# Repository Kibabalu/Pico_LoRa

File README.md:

# Pico LoRa Node

LoRa Node based on Raspberry Pi Pico and LoRa board RFM95

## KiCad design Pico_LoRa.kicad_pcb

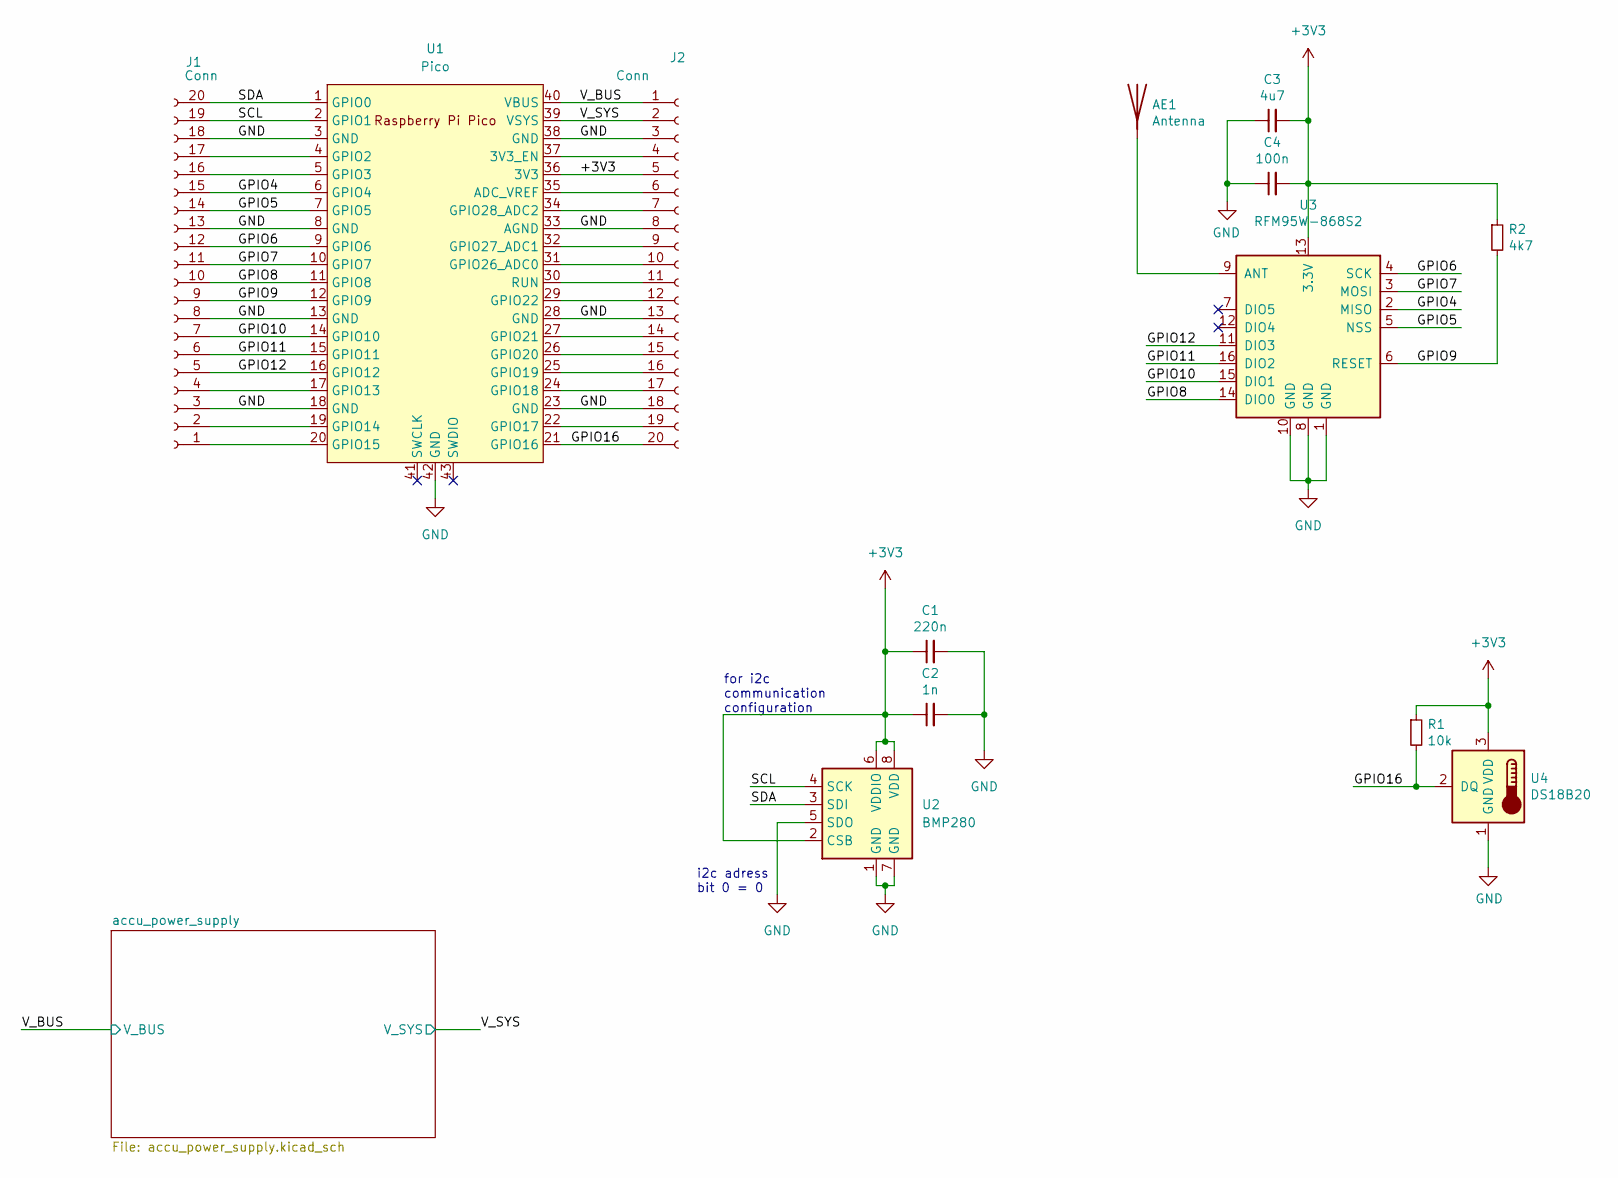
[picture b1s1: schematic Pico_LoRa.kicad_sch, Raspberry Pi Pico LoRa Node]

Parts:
AE1: Antenna; PinHeader_1x01_P2.54mm_Vertical
C1: 220n; C_0805_2012Metric_Pad1.18x1.45mm_HandSolder
C2: 1n; C_0805_2012Metric_Pad1.18x1.45mm_HandSolder
C3: 4u7; C_0805_2012Metric_Pad1.18x1.45mm_HandSolder
C4: 100n; C_0805_2012Metric_Pad1.18x1.45mm_HandSolder
J1, J2: Conn; PinSocket_1x20_P2.54mm_Vertical
R1: 10k; R_0805_2012Metric_Pad1.20x1.40mm_HandSolder
R2: 4k7; R_0805_2012Metric_Pad1.20x1.40mm_HandSolder
U1: Pico; RPi_Pico_SMD_TH
U2: BMP280; Bosch_LGA-8_2x2.5mm_P0.65mm_ClockwisePinNumbering
U3: RFM95W-868S2; HOPERF_RFM9XW_SMD
U4: DS18B20; TO-92_Inline

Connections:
+3V3: C1.1, C2.1, C3.2, C4.2, J2.5, R1.1, R2.1, U1.36 (3V3), U2.2 (CSB), U2.6 (VDDIO), U2.8 (VDD), U3.13 (3.3V), U4.3 (VDD)
/GPIO4: J1.15, U1.6 (GPIO4), U3.2 (MISO)
/GPIO5: J1.14, U1.7 (GPIO5), U3.5 (NSS)
/GPIO6: J1.12, U1.9 (GPIO6), U3.4 (SCK)
/GPIO7: J1.11, U1.10 (GPIO7), U3.3 (MOSI)
/GPIO8: J1.10, U1.11 (GPIO8), U3.14 (DIO0)
/GPIO9: J1.9, R2.2, U1.12 (GPIO9), U3.6 (RESET)
/GPIO10: J1.7, U1.14 (GPIO10), U3.15 (DIO1)
/GPIO11: J1.6, U1.15 (GPIO11), U3.16 (DIO2)
/GPIO12: J1.5, U1.16 (GPIO12), U3.11 (DIO3)
/GPIO16: J2.20, R1.2, U1.21 (GPIO16), U4.2 (DQ)
/SCL: J1.19, U1.2 (GPIO1), U2.4 (SCK)
/SDA: J1.20, U1.1 (GPIO0), U2.3 (SDI)
/V_BUS: J2.1, U1.40 (VBUS); also elsewhere on the board
/V_SYS: J2.2, U1.39 (VSYS); also elsewhere on the board
GND: C1.2, C2.2, C3.1, C4.1, J1.3, J1.8, J1.13, J1.18, J2.3, J2.8, J2.13, J2.18, U1.3 (GND), U1.8 (GND), U1.13 (GND), U1.18 (GND), U1.23 (GND), U1.28 (GND), U1.33 (AGND), U1.38 (GND), U1.42 (GND), U2.1 (GND), U2.5 (SDO), U2.7 (GND), U3.1 (GND), U3.8 (GND), U3.10 (GND), U4.1 (GND); also elsewhere on the board
unnamed: AE1.1 (A), U3.9 (ANT)
unnamed: J1.1, U1.20 (GPIO15)
unnamed: J1.2, U1.19 (GPIO14)
unnamed: J1.4, U1.17 (GPIO13)
unnamed: J1.16, U1.5 (GPIO3)
unnamed: J1.17, U1.4 (GPIO2)
unnamed: J2.4, U1.37 (3V3_EN)
unnamed: J2.6, U1.35 (ADC_VREF)
unnamed: J2.7, U1.34 (GPIO28_ADC2)
unnamed: J2.9, U1.32 (GPIO27_ADC1)
unnamed: J2.10, U1.31 (GPIO26_ADC0)
unnamed: J2.11, U1.30 (RUN)
unnamed: J2.12, U1.29 (GPIO22)
unnamed: J2.14, U1.27 (GPIO21)
unnamed: J2.15, U1.26 (GPIO20)
unnamed: J2.16, U1.25 (GPIO19)
unnamed: J2.17, U1.24 (GPIO18)
unnamed: J2.19, U1.22 (GPIO17)

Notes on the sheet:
for i2c communication configuration
i2c adress bit 0 = 0

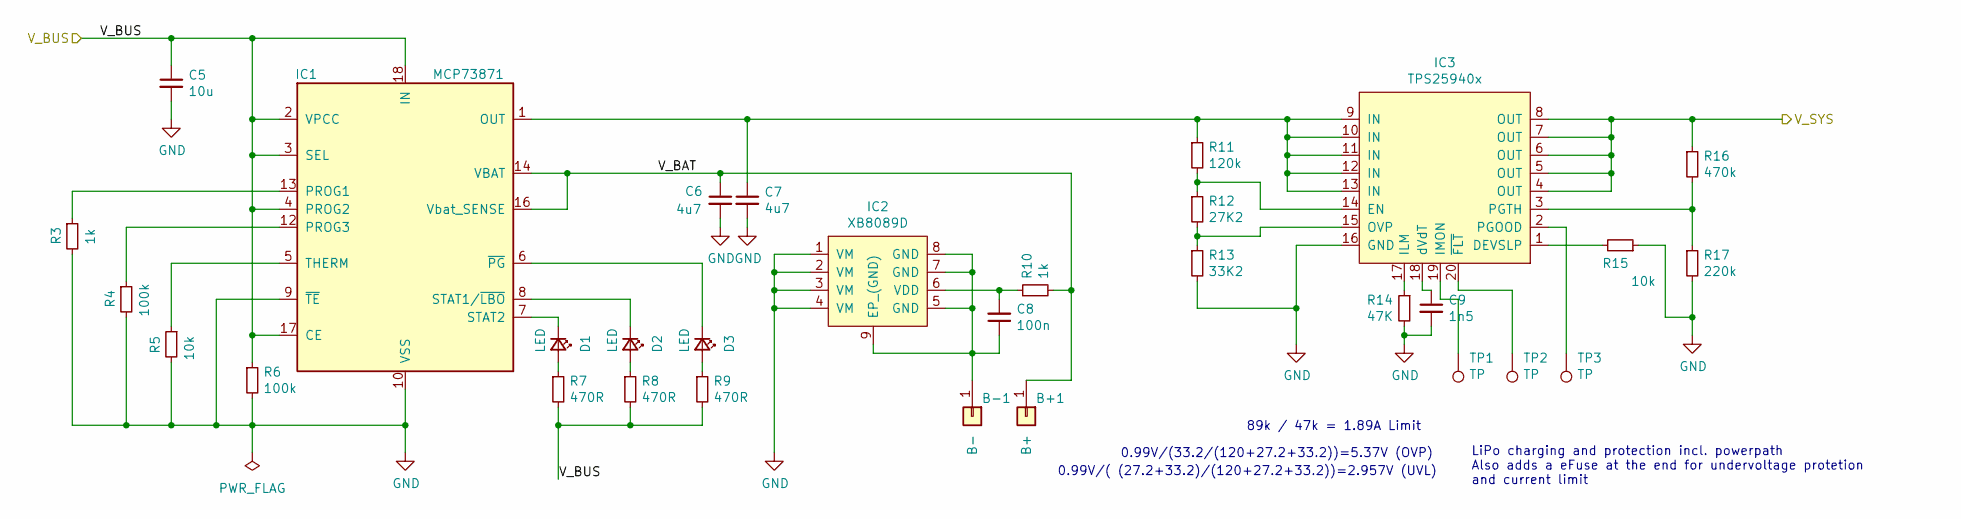
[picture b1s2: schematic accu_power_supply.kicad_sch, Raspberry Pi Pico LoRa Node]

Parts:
B+1: B+; SolderWirePad_1x01_SMD_1x2mm
B-1: B-; SolderWirePad_1x01_SMD_1x2mm
C5: 10u; C_0805_2012Metric_Pad1.18x1.45mm_HandSolder
C6, C7: 4u7; C_0805_2012Metric_Pad1.18x1.45mm_HandSolder
C8: 100n; C_0805_2012Metric_Pad1.18x1.45mm_HandSolder
C9: 1n5; C_0805_2012Metric_Pad1.18x1.45mm_HandSolder
D1, D2, D3: LED; LED_0805_2012Metric_Pad1.15x1.40mm_HandSolder
IC1: MCP73871; QFN-20-1EP_4x4mm_P0.5mm_EP2.5x2.5mm
IC2: XB8089D
IC3: TPS25940x; TI_WQFN_20_EP
R3, R10: 1k; R_0805_2012Metric_Pad1.20x1.40mm_HandSolder
R4, R6: 100k; R_0805_2012Metric_Pad1.20x1.40mm_HandSolder
R5, R15: 10k; R_0805_2012Metric_Pad1.20x1.40mm_HandSolder
R7, R8, R9: 470R; R_0805_2012Metric_Pad1.20x1.40mm_HandSolder
R11: 120k; R_0805_2012Metric_Pad1.20x1.40mm_HandSolder
R12: 27K2; R_0805_2012Metric_Pad1.20x1.40mm_HandSolder
R13: 33K2; R_0805_2012Metric_Pad1.20x1.40mm_HandSolder
R14: 47K; R_0805_2012Metric_Pad1.20x1.40mm_HandSolder
R16: 470k; R_0805_2012Metric_Pad1.20x1.40mm_HandSolder
R17: 220k; R_0805_2012Metric_Pad1.20x1.40mm_HandSolder
TP1, TP2, TP3: TP; TestPoint_Pad_D1.0mm

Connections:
/V_BUS: C5.1, IC1.2 (VPCC), IC1.3 (SEL), IC1.4 (PROG2), IC1.17 (CE), IC1.18 (IN), IC1.19 (IN), R6.1, R7.2, R8.2, R9.2; also elsewhere on the board
/V_SYS: IC3.4 (OUT), IC3.5 (OUT), IC3.6 (OUT), IC3.7 (OUT), IC3.8 (OUT), R16.1; also elsewhere on the board
/accu_power_supply/V_BAT: B+1.1, C6.1, IC1.14 (VBAT), IC1.15 (VBAT), IC1.16 (Vbat_SENSE), R10.2
GND: C5.2, C6.2, C7.2, C9.2, IC1.9 (~TE), IC1.10 (VSS), IC1.11 (VSS), IC1.21 (VSS), IC2.1 (VM), IC2.2 (VM), IC2.3 (VM), IC2.4 (VM), IC3.16 (GND), R3.2, R4.2, R5.2, R6.2, R13.2, R14.2, R15.1, R17.2; also elsewhere on the board
unnamed: B-1.1, C8.1, IC2.5 (GND), IC2.7 (GND), IC2.8 (GND), IC2.9 (EP_(GND))
unnamed: C7.1, IC1.1 (OUT), IC1.20 (OUT), IC3.9 (IN), IC3.10 (IN), IC3.11 (IN), IC3.12 (IN), IC3.13 (IN), R11.1
unnamed: C8.2, IC2.6 (VDD), R10.1
unnamed: C9.1, IC3.18 (dVdT)
unnamed: D1.1 (K), IC1.7 (STAT2)
unnamed: D1.2 (A), R7.1
unnamed: D2.1 (K), IC1.8 (STAT1/~LBO)
unnamed: D2.2 (A), R8.1
unnamed: D3.1 (K), IC1.6 (~PG)
unnamed: D3.2 (A), R9.1
unnamed: IC1.5 (THERM), R5.1
unnamed: IC1.12 (PROG3), R4.1
unnamed: IC1.13 (PROG1), R3.1
unnamed: IC3.1 (DEVSLP), R15.2
unnamed: IC3.2 (PGOOD), TP3.1
unnamed: IC3.3 (PGTH), R16.2, R17.1
unnamed: IC3.14 (EN), R11.2, R12.1
unnamed: IC3.15 (OVP), R12.2, R13.1
unnamed: IC3.17 (ILM), R14.1
unnamed: IC3.19 (IMON), TP1.1
unnamed: IC3.20 (~FLT), TP2.1

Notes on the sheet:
89k / 47k = 1.89A Limit
LiPo charging and protection incl. powerpath Also adds a eFuse at the end for undervoltage protetion and current limit
0.99V/(33.2/(120+27.2+33.2))=5.37V (OVP)
0.99V/( (27.2+33.2)/(120+27.2+33.2))=2.957V (UVL)

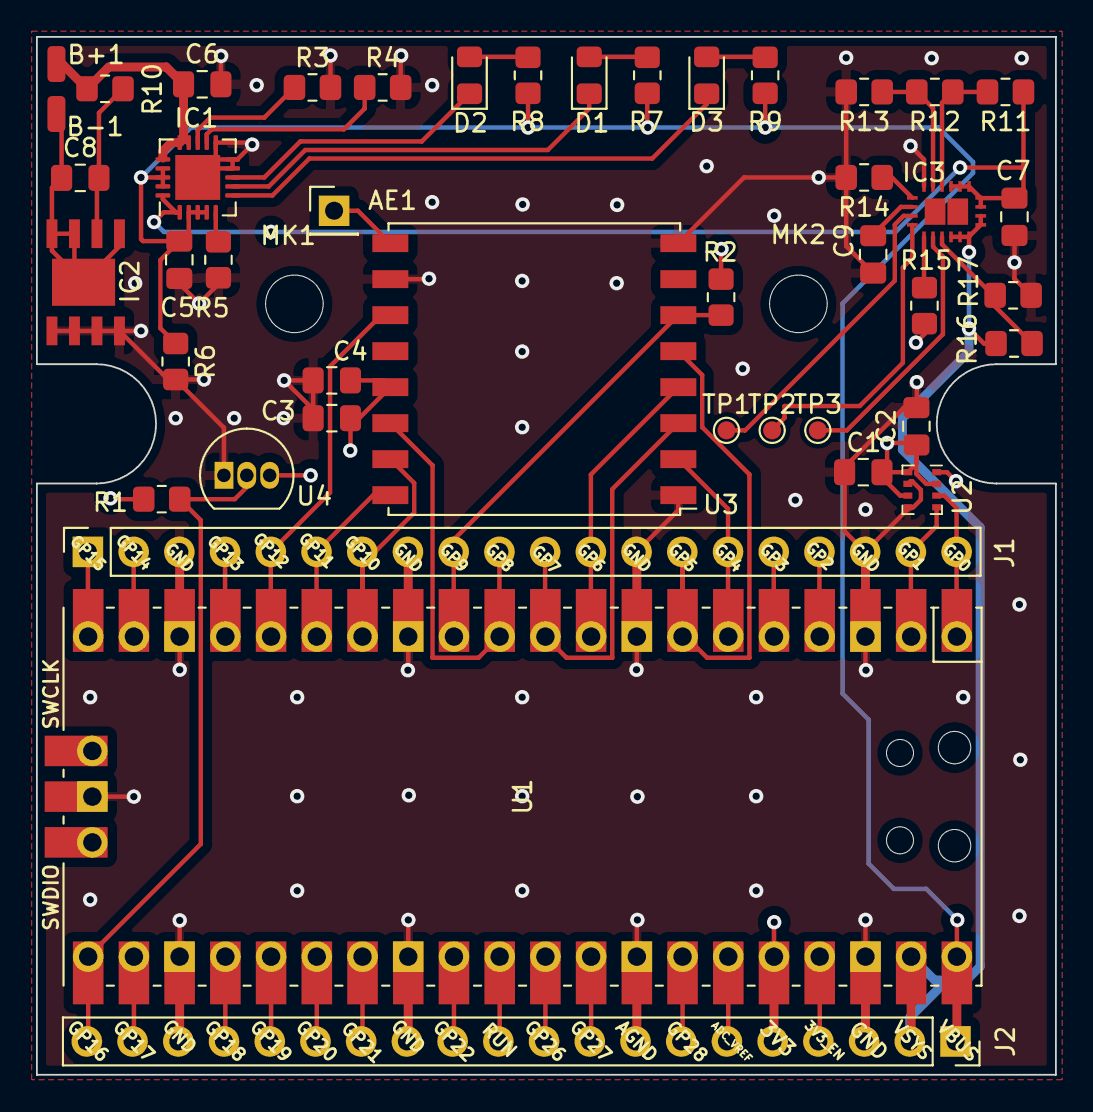
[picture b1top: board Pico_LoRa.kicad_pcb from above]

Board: 4 copper layers, 56.6 x 57.7 mm, 46 parts (0 on the bottom side), 56 nets.

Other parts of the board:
MK1, MK2: Mounting_Hole; MountingHole_3.2mm_M3_ISO7380

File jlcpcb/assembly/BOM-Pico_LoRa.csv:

Comment,Designator,Footprint,LCSC
LED,D3,LED_0805_2012Metric_Pad1.15x1.40mm_HandSolder,
47K,R14,R_0805_2012Metric_Pad1.20x1.40mm_HandSolder,
220k,R17,R_0805_2012Metric_Pad1.20x1.40mm_HandSolder,
470R,R8,R_0805_2012Metric_Pad1.20x1.40mm_HandSolder,
10k,R1,R_0805_2012Metric_Pad1.20x1.40mm_HandSolder,
TPS25940x,IC3,TI_WQFN_20_EP,
LED,D2,LED_0805_2012Metric_Pad1.15x1.40mm_HandSolder,
DS18B20,U4,TO-92_Inline,
Conn,J2,PinSocket_1x20_P2.54mm_Vertical,
1n5,C9,C_0805_2012Metric_Pad1.18x1.45mm_HandSolder,
TP,TP2,TestPoint_Pad_D1.0mm,
470k,R16,R_0805_2012Metric_Pad1.20x1.40mm_HandSolder,
10k,R15,R_0805_2012Metric_Pad1.20x1.40mm_HandSolder,
4u7,C3,C_0805_2012Metric_Pad1.18x1.45mm_HandSolder,
27K2,R12,R_0805_2012Metric_Pad1.20x1.40mm_HandSolder,
BMP280,U2,Bosch_LGA-8_2x2.5mm_P0.65mm_ClockwisePinNumbering,
TP,TP1,TestPoint_Pad_D1.0mm,
Pico,U1,RPi_Pico_SMD_TH,
Antenna,AE1,PinHeader_1x01_P2.54mm_Vertical,
120k,R11,R_0805_2012Metric_Pad1.20x1.40mm_HandSolder,
4u7,C7,C_0805_2012Metric_Pad1.18x1.45mm_HandSolder,
RFM95W-868S2,U3,HOPERF_RFM9XW_SMD,
4k7,R2,R_0805_2012Metric_Pad1.20x1.40mm_HandSolder,
33K2,R13,R_0805_2012Metric_Pad1.20x1.40mm_HandSolder,
4u7,C6,C_0805_2012Metric_Pad1.18x1.45mm_HandSolder,
10k,R5,R_0805_2012Metric_Pad1.20x1.40mm_HandSolder,
1n,C2,C_0805_2012Metric_Pad1.18x1.45mm_HandSolder,
TP,TP3,TestPoint_Pad_D1.0mm,
10u,C5,C_0805_2012Metric_Pad1.18x1.45mm_HandSolder,
1k,R3,R_0805_2012Metric_Pad1.20x1.40mm_HandSolder,
100k,R4,R_0805_2012Metric_Pad1.20x1.40mm_HandSolder,
100n,C8,C_0805_2012Metric_Pad1.18x1.45mm_HandSolder,
100n,C4,C_0805_2012Metric_Pad1.18x1.45mm_HandSolder,
Conn,J1,PinSocket_1x20_P2.54mm_Vertical,
MCP73871,IC1,QFN-20-1EP_4x4mm_P0.5mm_EP2.5x2.5mm,
470R,R9,R_0805_2012Metric_Pad1.20x1.40mm_HandSolder,
220n,C1,C_0805_2012Metric_Pad1.18x1.45mm_HandSolder,
100k,R6,R_0805_2012Metric_Pad1.20x1.40mm_HandSolder,
LED,D1,LED_0805_2012Metric_Pad1.15x1.40mm_HandSolder,
470R,R7,R_0805_2012Metric_Pad1.20x1.40mm_HandSolder,
1k,R10,R_0805_2012Metric_Pad1.20x1.40mm_HandSolder,
XB8089D,IC2,XB8089D,

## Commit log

2022-01-31 1st commit of the board ordered by Aisler
2022-01-31 rendering of the board
2022-01-31 some more documentation
2022-01-31 more pics
2022-01-31 some cleaning
2022-02-06 some more GND vias
2022-02-06 new 3D rendering
2022-02-11 enclosure pic added
